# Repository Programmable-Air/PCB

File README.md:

# PCB

## Pre-order at [CrowdSupply](https://www.crowdsupply.com/tinkrmind/programmable-air)

PCB for Programmable-Air

The electronics for Programmable-Air are pretty simple, as these things go. The PCB is composed of two boards that are connected by default but can be snapped off and used independently. The 'master' board contains an Arduino Nano, two pumps and IO. The 'slave' board contains three valves and the pressure sensor circuit. In this way, the 'master' board contains the brains and IO as well as the pressure sources while the 'slave' board contains the valves to control air flow and feedback from the pressure sensor. The 'master' board contains connectors to attach two more slave boards, thus allowing you to control three independent soft robots with the same Arduino. However, most of the time you'd probably only use the boards in their default configuration.

Below is the pin definition for the v0.5 of the board:

Here are the functions of all the Pins:

* __Power:__
	* __Vin(+12V)__ - from the external power source
	* __+5V__ - Regulated 5V from Arduino's linear 5V regulator
	* __GND__ - Common ground for all signals

* __Connections on master board:__
	* __D10__ - Drives the base of the transistor for Motor 1
	* __D11__ - Drives the base of the transistor for Motor 2
	* __D12__ - Drives the three onboard neopixels(for debugging and such)
	* __D13__ - Drives the base of the Load transistor. The collector of the Load is broken out as Load. You can connect it to an external pump or relay for regulating them.
	* __D2__ - Connected to the __blue__ button, pulled up using the internal 20K resistor and connects to ground when button is pressed
	* __D3__ - Connected to the __red__ button, pulled up using the internal 20K resistor and connects to ground when button is pressed
	* __AREF__ - Connected to a LM4040 +5V voltage reference

* __Connections to slave boards__
	* __Board 0__
		* __A3__ - Pressure sensor output(on the valve board). Can be used as a GPIO if slave board is not connected. Range~ 1V-4V
		* __D4__ - Drives Valve #02 via a transistor(on the valve board). Can be used as a GPIO if slave board is not connected.
		* __D5__ - Drives Valve #01 via a transistor(on the valve board). Can be used as a GPIO if slave board is not connected.
		* __D6__ - Drives Valve #00 via a transistor(on the valve board). Can be used as a GPIO if slave board is not connected.

	* __Board 1__
		 * __A2__ - Pressure sensor output(on the valve board). Can be used as a GPIO if slave board is not connected. Range~ 1V-4V
		 * __D9__ - Drives Valve #12 via a transistor(on the valve board). Can be used as a GPIO if slave board is not connected.
		 * __D8__ - Drives Valve #11 via a transistor(on the valve board). Can be used as a GPIO if slave board is not connected.
		 * __D7__ - Drives Valve #10 via a transistor(on the valve board). Can be used as a GPIO if slave board is not connected.

	* __Board 2__
		 * __A5__ - Pressure sensor output(on the valve board). Can be used as a GPIO if slave board is not connected. Range~ 1V-4V
		 * __A4__ - Drives Valve #22 via a transistor(on the valve board). Can be used as a GPIO if slave board is not connected.
		 * __A1__ - Drives Valve #21 via a transistor(on the valve board). Can be used as a GPIO if slave board is not connected.
		 * __A0__ - Drives Valve #20 via a transistor(on the valve board). Can be used as a GPIO if slave board is not connected.

The yellow, green and white button are connected to the base of the transistors driving their respective valves and override the signal from the Arduino. They are intended to be used for testing a new soft robot without any coding.

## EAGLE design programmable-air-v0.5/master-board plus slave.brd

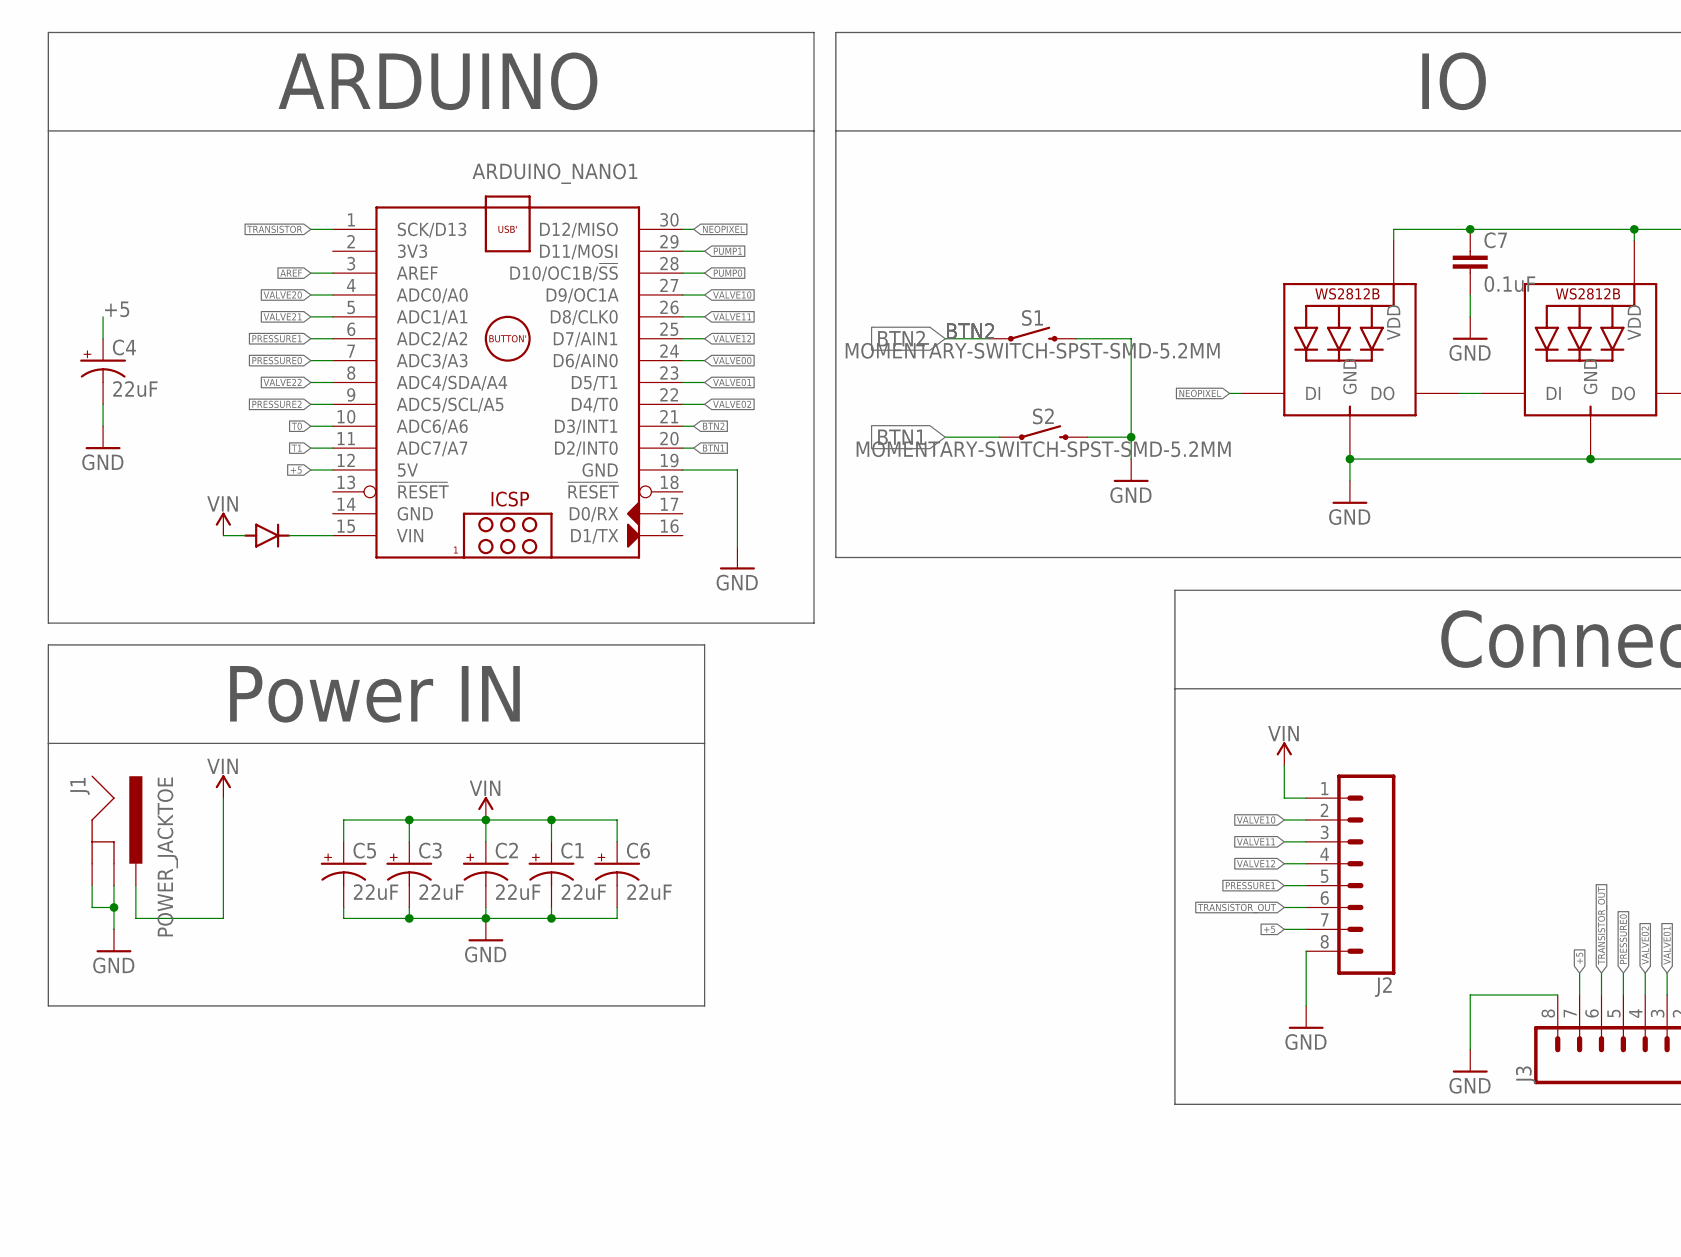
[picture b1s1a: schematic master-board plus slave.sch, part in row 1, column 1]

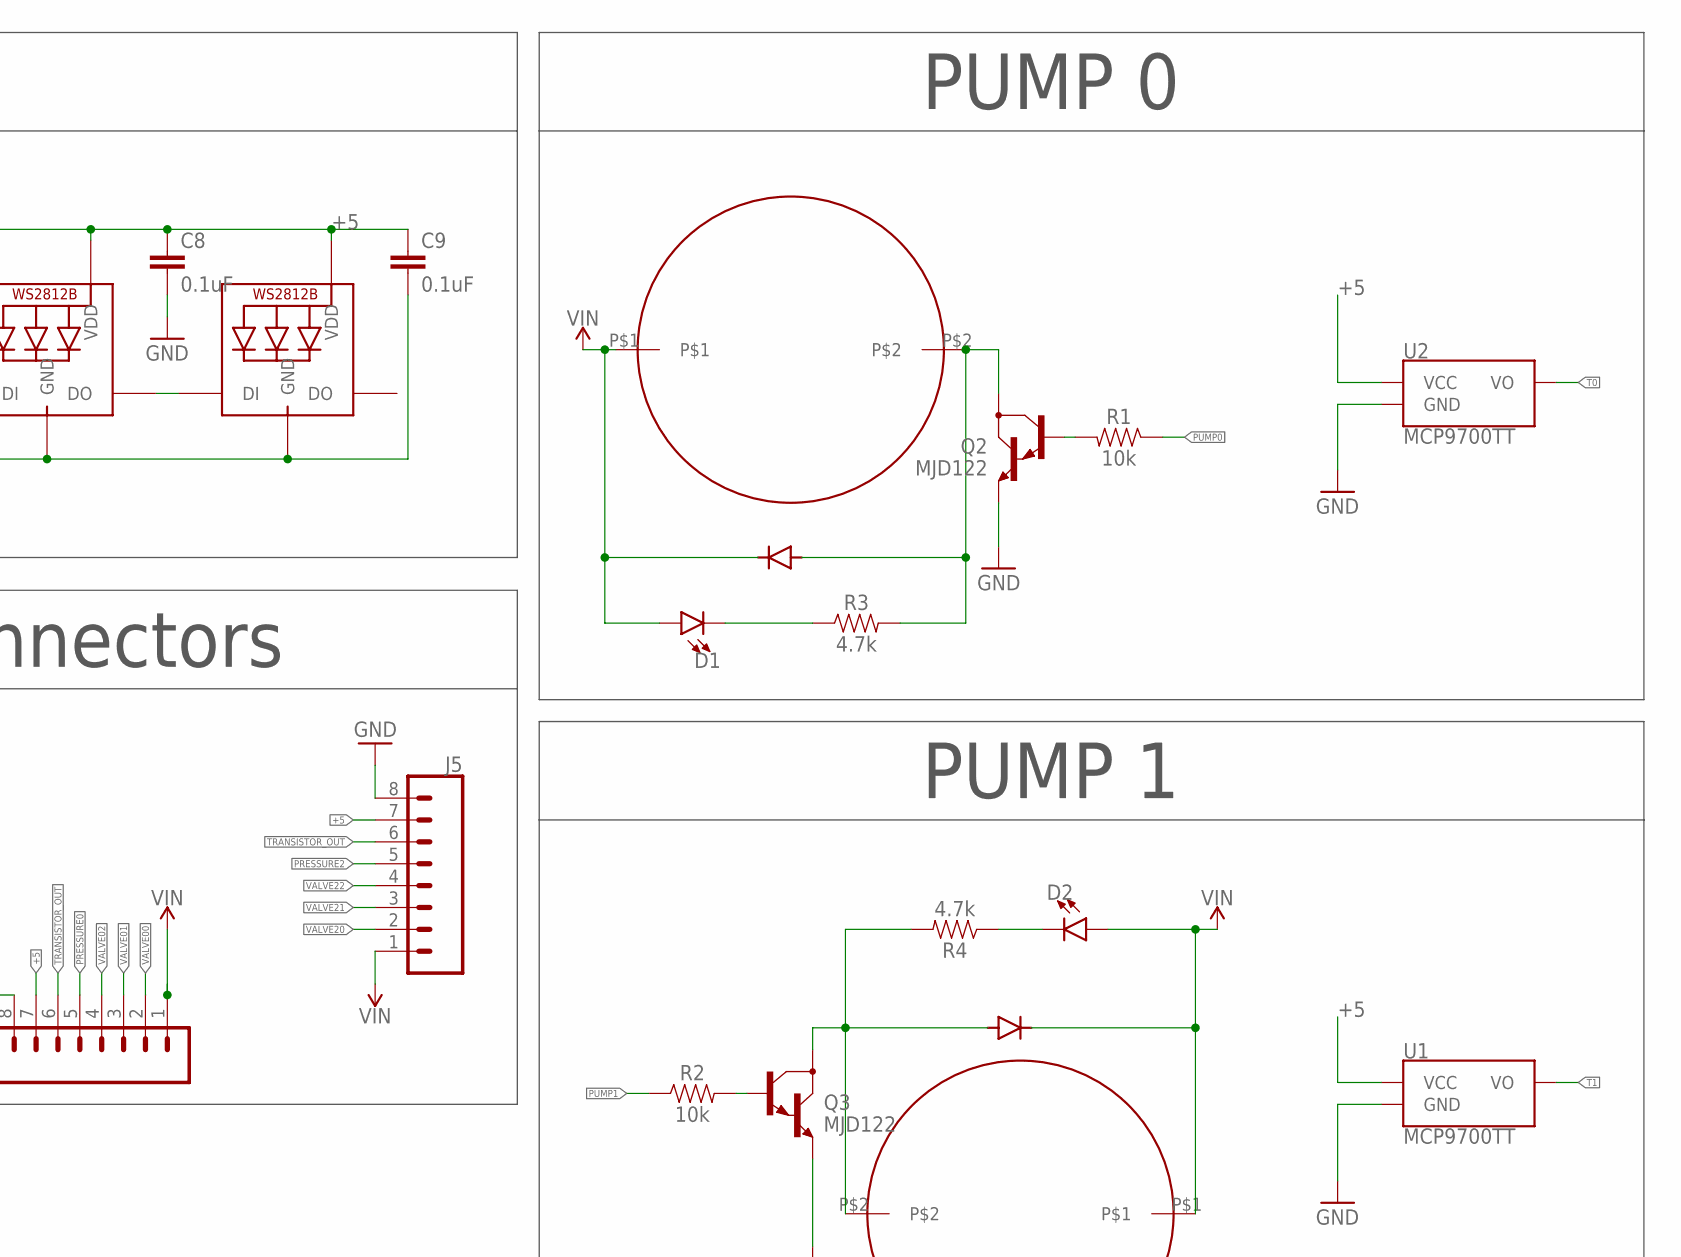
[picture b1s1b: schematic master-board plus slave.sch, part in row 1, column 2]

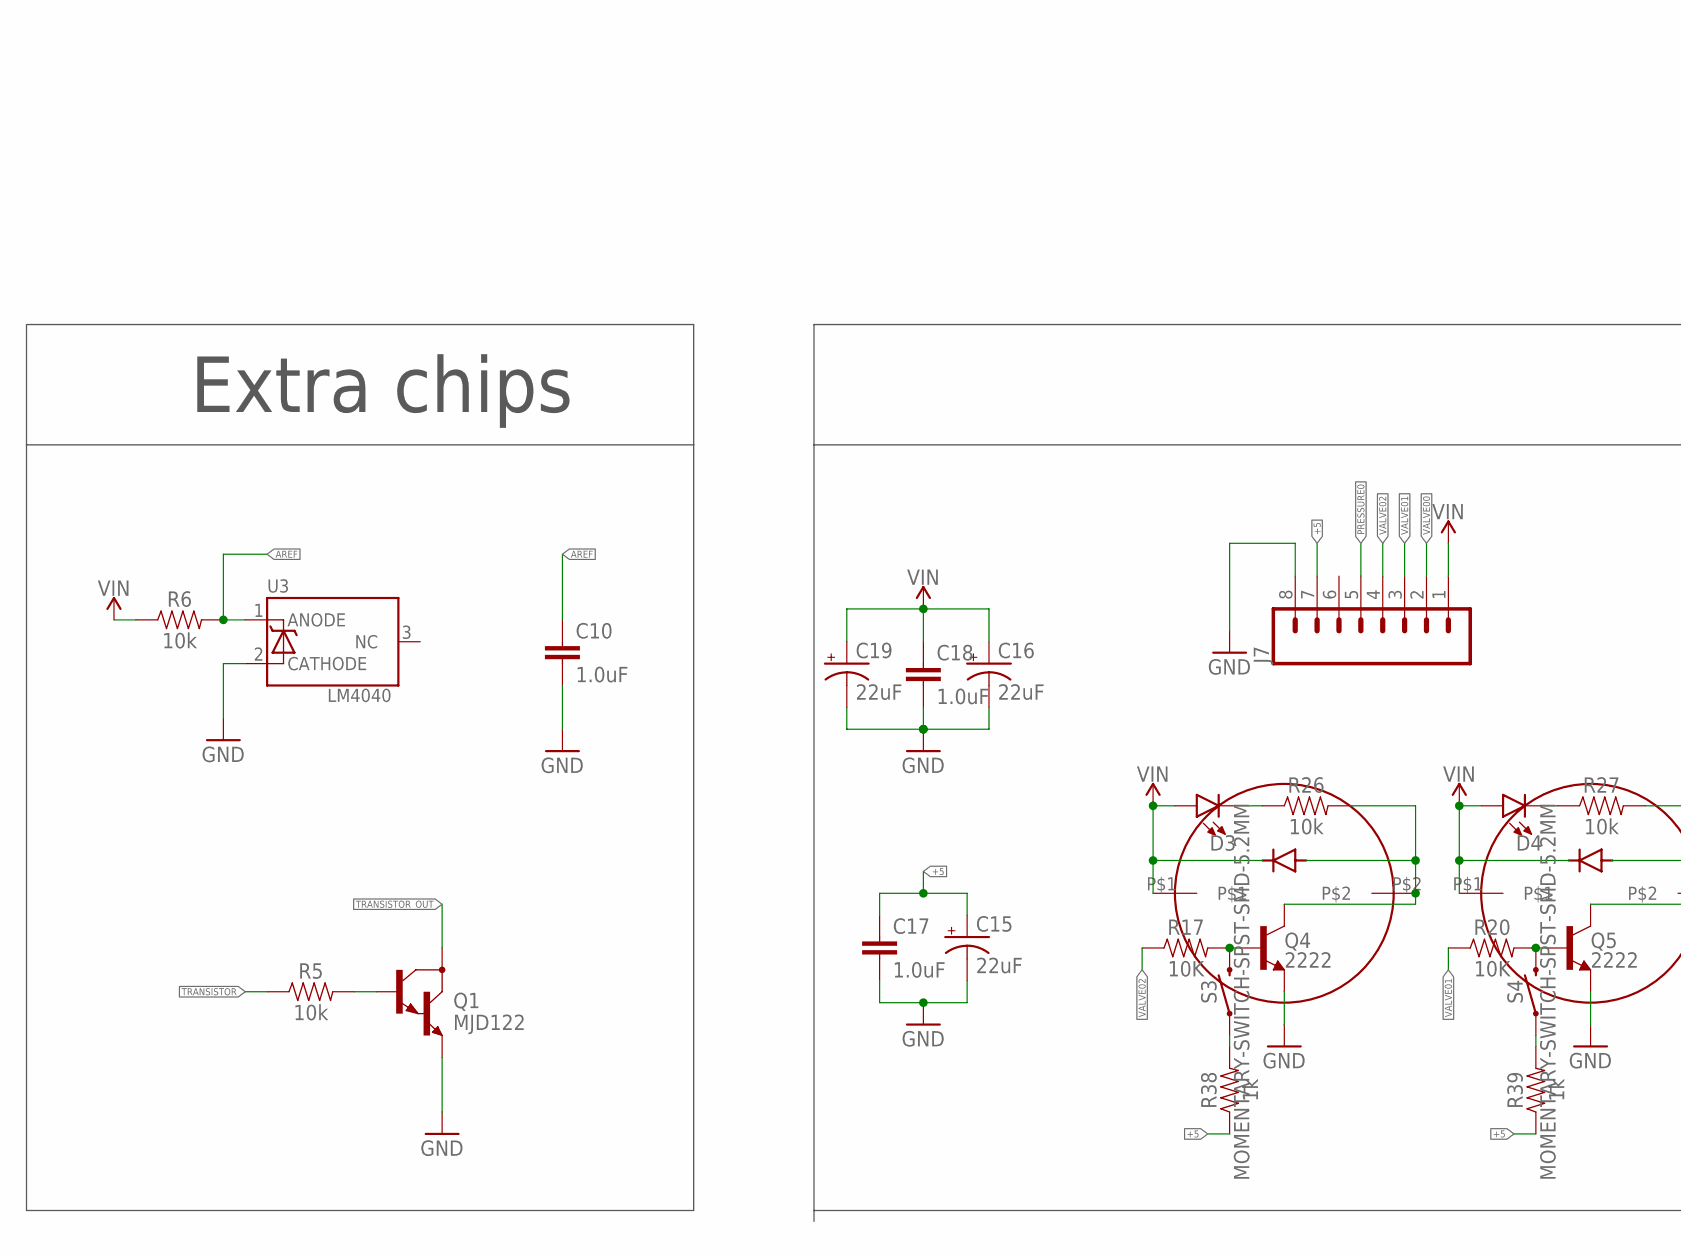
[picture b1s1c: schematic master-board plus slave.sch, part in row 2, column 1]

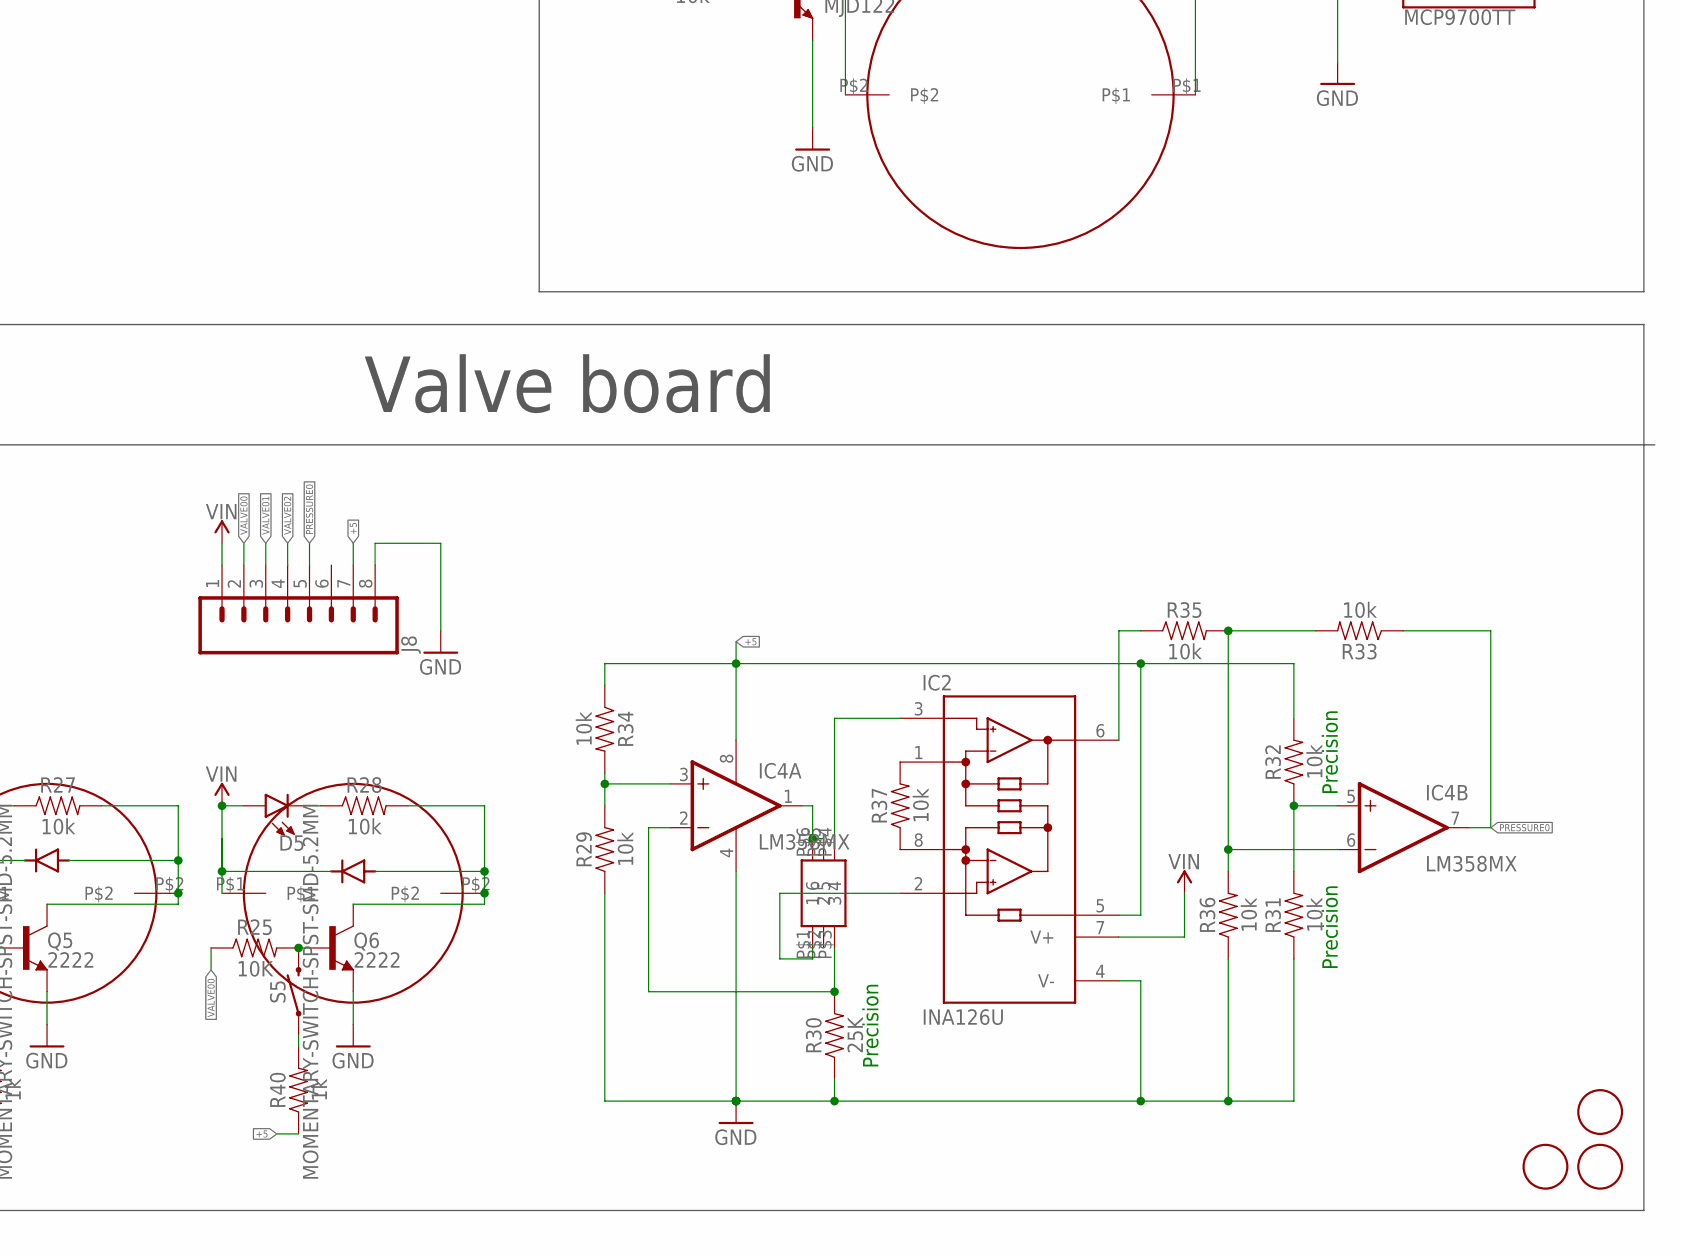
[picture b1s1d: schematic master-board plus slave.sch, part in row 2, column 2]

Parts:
ARDUINO_NANO1: ARDUINO_NANO
C1, C2, C3, C4, C5, C6, C15, C16, C19: 22uF; PANASONIC_C
C7, C8, C9: 0.1uF; 0603
C10, C17, C18: 1.0uF; 0603
D1, D2, D3, D4, D5: LED0603; LED-0603
IC2: INA126U; SO08
IC4: LM358MX; SO08
J1: POWER_JACKTOE; POWER_JACK_SMD_OVERPASTE_TOE
J2: CONN_08FLIPPED; 1X08
J3: CONN_08"; 1X08
J5: CONN_081X08_FEMALE_FLIPPED; 1X08_FEMALE_FLIPPED
J7: CONN_08; 1X08_MALE_FLIPPED
J8: CONN_08NO_SILK_FEMALE_PTH; 1X08_NO_SILK
LED1, LED2, LED3: WS2812B5050; WS2812B
Q1, Q2, Q3: MJD122; DPAK
Q4, Q5, Q6: 2222; SOT23-3
R1, R2, R5, R6, R26, R27, R28, R29, R31, R32, R33, R34, R35, R36, R37: 10k; 0603
R3, R4: 4.7k; 0603
R17, R20, R25: 10K; 0603
R30: 25K; 0603
R38, R39, R40: 1k; 0603
S1, S2, S3, S4, S5: MOMENTARY-SWITCH-SPST-SMD-5.2MM; TACTILE_SWITCH_SMD_5.2MM
U1, U2: MCP9700TT; SOT23-3
U3: LM4040; SOT23-3
U$1, U$2: AIYIMA-PUMP-A5F083; A5F083
U$3, U$4, U$7, U$20, U$21, U$22: IN4148; SOD123
U$10, U$11, U$12: FIDUCIAL; FIDUCIAL_1MM
U$17, U$18, U$19: CJV23-SOLENOID-VALVE; CJV23
U$23: 2SMPP-03

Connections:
+5: ARDUINO_NANO1.12 (5V), C4.+, C7.1, C8.1, C9.1, C15.+, C17.1, IC2.5 (REF), IC4.8 (V+), J2.7, J3.7, J5.7, J7.7, J8.7, LED1.1-VDD (VDD), LED2.1-VDD (VDD), LED3.1-VDD (VDD), R32.2, R34.1, R38.1, R39.1, R40.1, U1.1 (VCC), U2.1 (VCC)
AREF: ARDUINO_NANO1.3 (AREF), C10.1, R6.2, U3.1 (ANODE)
BTN1: ARDUINO_NANO1.20 (D2/INT0), S2.1
BTN2: ARDUINO_NANO1.21 (D3/INT1), S1.1
GND: ARDUINO_NANO1.14 (GND), ARDUINO_NANO1.19 (GND), C1.-, C2.-, C3.-, C4.-, C5.-, C6.-, C7.2, C8.2, C9.2, C10.2, C15.-, C16.-, C17.2, C18.2, C19.-, IC2.4 (V-), IC4.4 (V-), J1.GND (GNDBREAK), J1.P$4 (GND), J2.8, J3.8, J5.8, J7.8, J8.8, LED1.3-GND (GND), LED2.3-GND (GND), LED3.3-GND (GND), Q1.3 (E), Q2.3 (E), Q3.3 (E), Q4.2 (E), Q5.2 (E), Q6.2 (E), R29.1, R30.1, R31.1, R36.1, S1.3 (2), S2.3 (2), U1.3 (GND), U2.3 (GND), U3.2 (CATHODE)
unnamed: ARDUINO_NANO1.15 (VIN), U$7.C
unnamed: Q3.1 (B), R2.2
unnamed: Q2.1 (B), R1.2
unnamed: Q2.4 (C), R3.2, U$1.P$2, U$3.A
unnamed: Q3.4 (C), R4.2, U$2.P$2, U$4.A
unnamed: Q1.1 (B), R5.2
unnamed: D1.C, R3.1
unnamed: D2.C, R4.1
unnamed: LED2.2-DOUT (DO), LED3.4-DIN (DI)
unnamed: LED1.2-DOUT (DO), LED2.4-DIN (DI)
unnamed: Q4.1 (B), R17.2, S3.3 (2)
unnamed: Q5.1 (B), R20.2, S4.3 (2)
unnamed: Q6.1 (B), R25.2, S5.3 (2)
unnamed: Q6.3 (C), R28.2, U$19.P$2, U$22.A
unnamed: Q5.3 (C), R27.2, U$18.P$2, U$21.A
unnamed: Q4.3 (C), R26.2, U$17.P$2, U$20.A
unnamed: D5.C, R28.1
unnamed: D4.C, R27.1
unnamed: D3.C, R26.1
unnamed: IC2.2 (-IN), U$23.P$1 (1)
unnamed: IC4.1 (OUT), U$23.P$5 (5), U$23.P$6 (6)
unnamed: IC2.3 (+IN), U$23.P$4 (4)
unnamed: IC4.3 (+IN), R29.2, R34.2
unnamed: IC2.8 (RG), R37.1
unnamed: IC2.1 (RG), R37.2
unnamed: IC4.6 (-IN), R33.2, R35.2, R36.2
unnamed: IC4.5 (+IN), R31.2, R32.1
unnamed: IC4.2 (-IN), R30.2, U$23.P$3 (3)
unnamed: IC2.6 (OUT), R35.1
unnamed: R38.2, S3.1
unnamed: R39.2, S4.1
unnamed: R40.2, S5.1
NEOPIXEL: ARDUINO_NANO1.30 (D12/MISO), LED1.4-DIN (DI)
PRESSURE0: ARDUINO_NANO1.7 (ADC3/A3), IC4.7 (OUT), J3.5, J7.5, J8.5, R33.1
PRESSURE1: ARDUINO_NANO1.6 (ADC2/A2), J2.5
PRESSURE2: ARDUINO_NANO1.9 (ADC5/SCL/A5), J5.5
PUMP0: ARDUINO_NANO1.28 (D10/OC1B/!SS), R1.1
PUMP1: ARDUINO_NANO1.29 (D11/MOSI), R2.1
T0: ARDUINO_NANO1.10 (ADC6/A6), U2.2 (VO)
T1: ARDUINO_NANO1.11 (ADC7/A7), U1.2 (VO)
TRANSISTOR: ARDUINO_NANO1.1 (SCK/D13), R5.1
TRANSISTOR_OUT: J2.6, J3.6, J5.6, Q1.4 (C)
VALVE00: ARDUINO_NANO1.24 (D6/AIN0), J3.2, J7.2, J8.2, R25.1
VALVE01: ARDUINO_NANO1.23 (D5/T1), J3.3, J7.3, J8.3, R20.1
VALVE02: ARDUINO_NANO1.22 (D4/T0), J3.4, J7.4, J8.4, R17.1
VALVE10: ARDUINO_NANO1.27 (D9/OC1A), J2.2
VALVE11: ARDUINO_NANO1.26 (D8/CLK0), J2.3
VALVE12: ARDUINO_NANO1.25 (D7/AIN1), J2.4
VALVE20: ARDUINO_NANO1.4 (ADC0/A0), J5.2
VALVE21: ARDUINO_NANO1.5 (ADC1/A1), J5.3
VALVE22: ARDUINO_NANO1.8 (ADC4/SDA/A4), J5.4
VIN: C1.+, C2.+, C3.+, C5.+, C6.+, C16.+, C18.1, C19.+, D1.A, D2.A, D3.A, D4.A, D5.A, IC2.7 (V+), J1.VIN0 (PWR), J2.1, J3.1, J5.1, J7.1, J8.1, R6.1, U$1.P$1, U$2.P$1, U$3.C, U$4.C, U$7.A, U$17.P$1, U$18.P$1, U$19.P$1, U$20.C, U$21.C, U$22.C

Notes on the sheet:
Precision
Power IN
PUMP 0
PUMP 1
ARDUINO
Connectors
Valve board
Extra chips

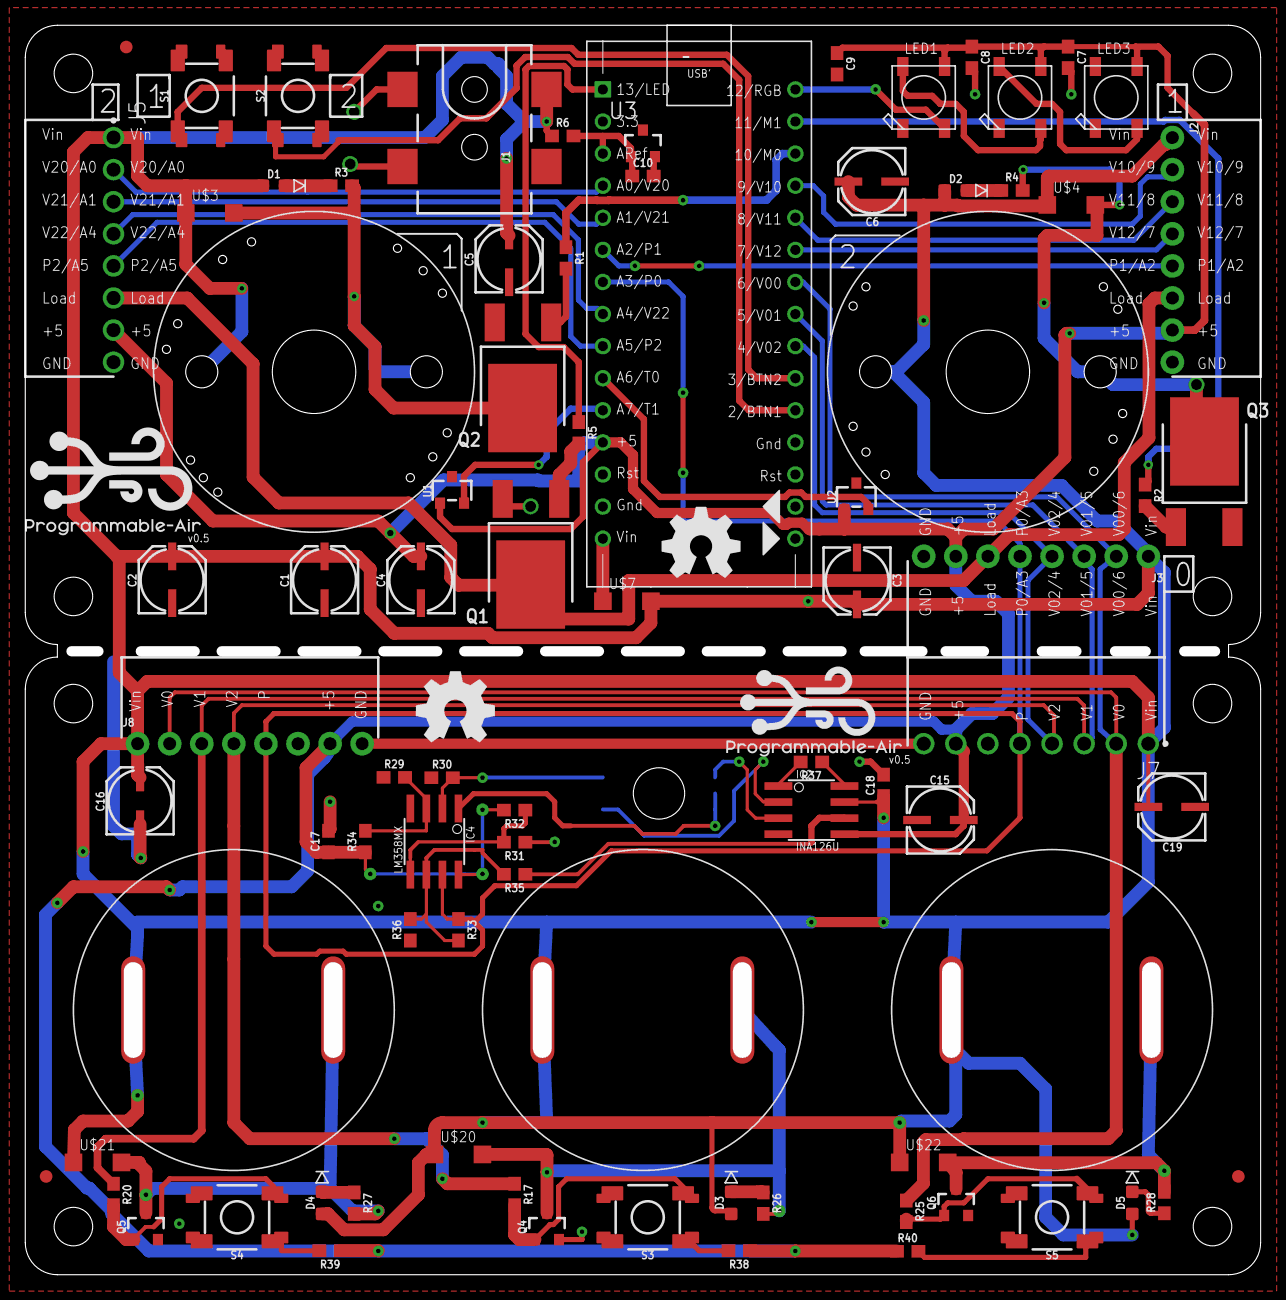
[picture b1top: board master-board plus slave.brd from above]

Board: 2 copper layers, 96.3 x 97.4 mm, 85 parts (0 on the bottom side), 57 nets.

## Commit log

2018-10-10 Initial Commit after sending v0.5 for production
2018-12-04 Added pin definitions and updated readme to contain pin definitions
2018-12-04 modified README and pinDefinitions
2018-12-04 Create LICENSE

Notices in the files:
parts and their libraries:
SparkFun-Sensors: Licensing: Creative Commons ShareAlike 4.0 International - https://creativecommons.org/licenses/by-sa/4.0
